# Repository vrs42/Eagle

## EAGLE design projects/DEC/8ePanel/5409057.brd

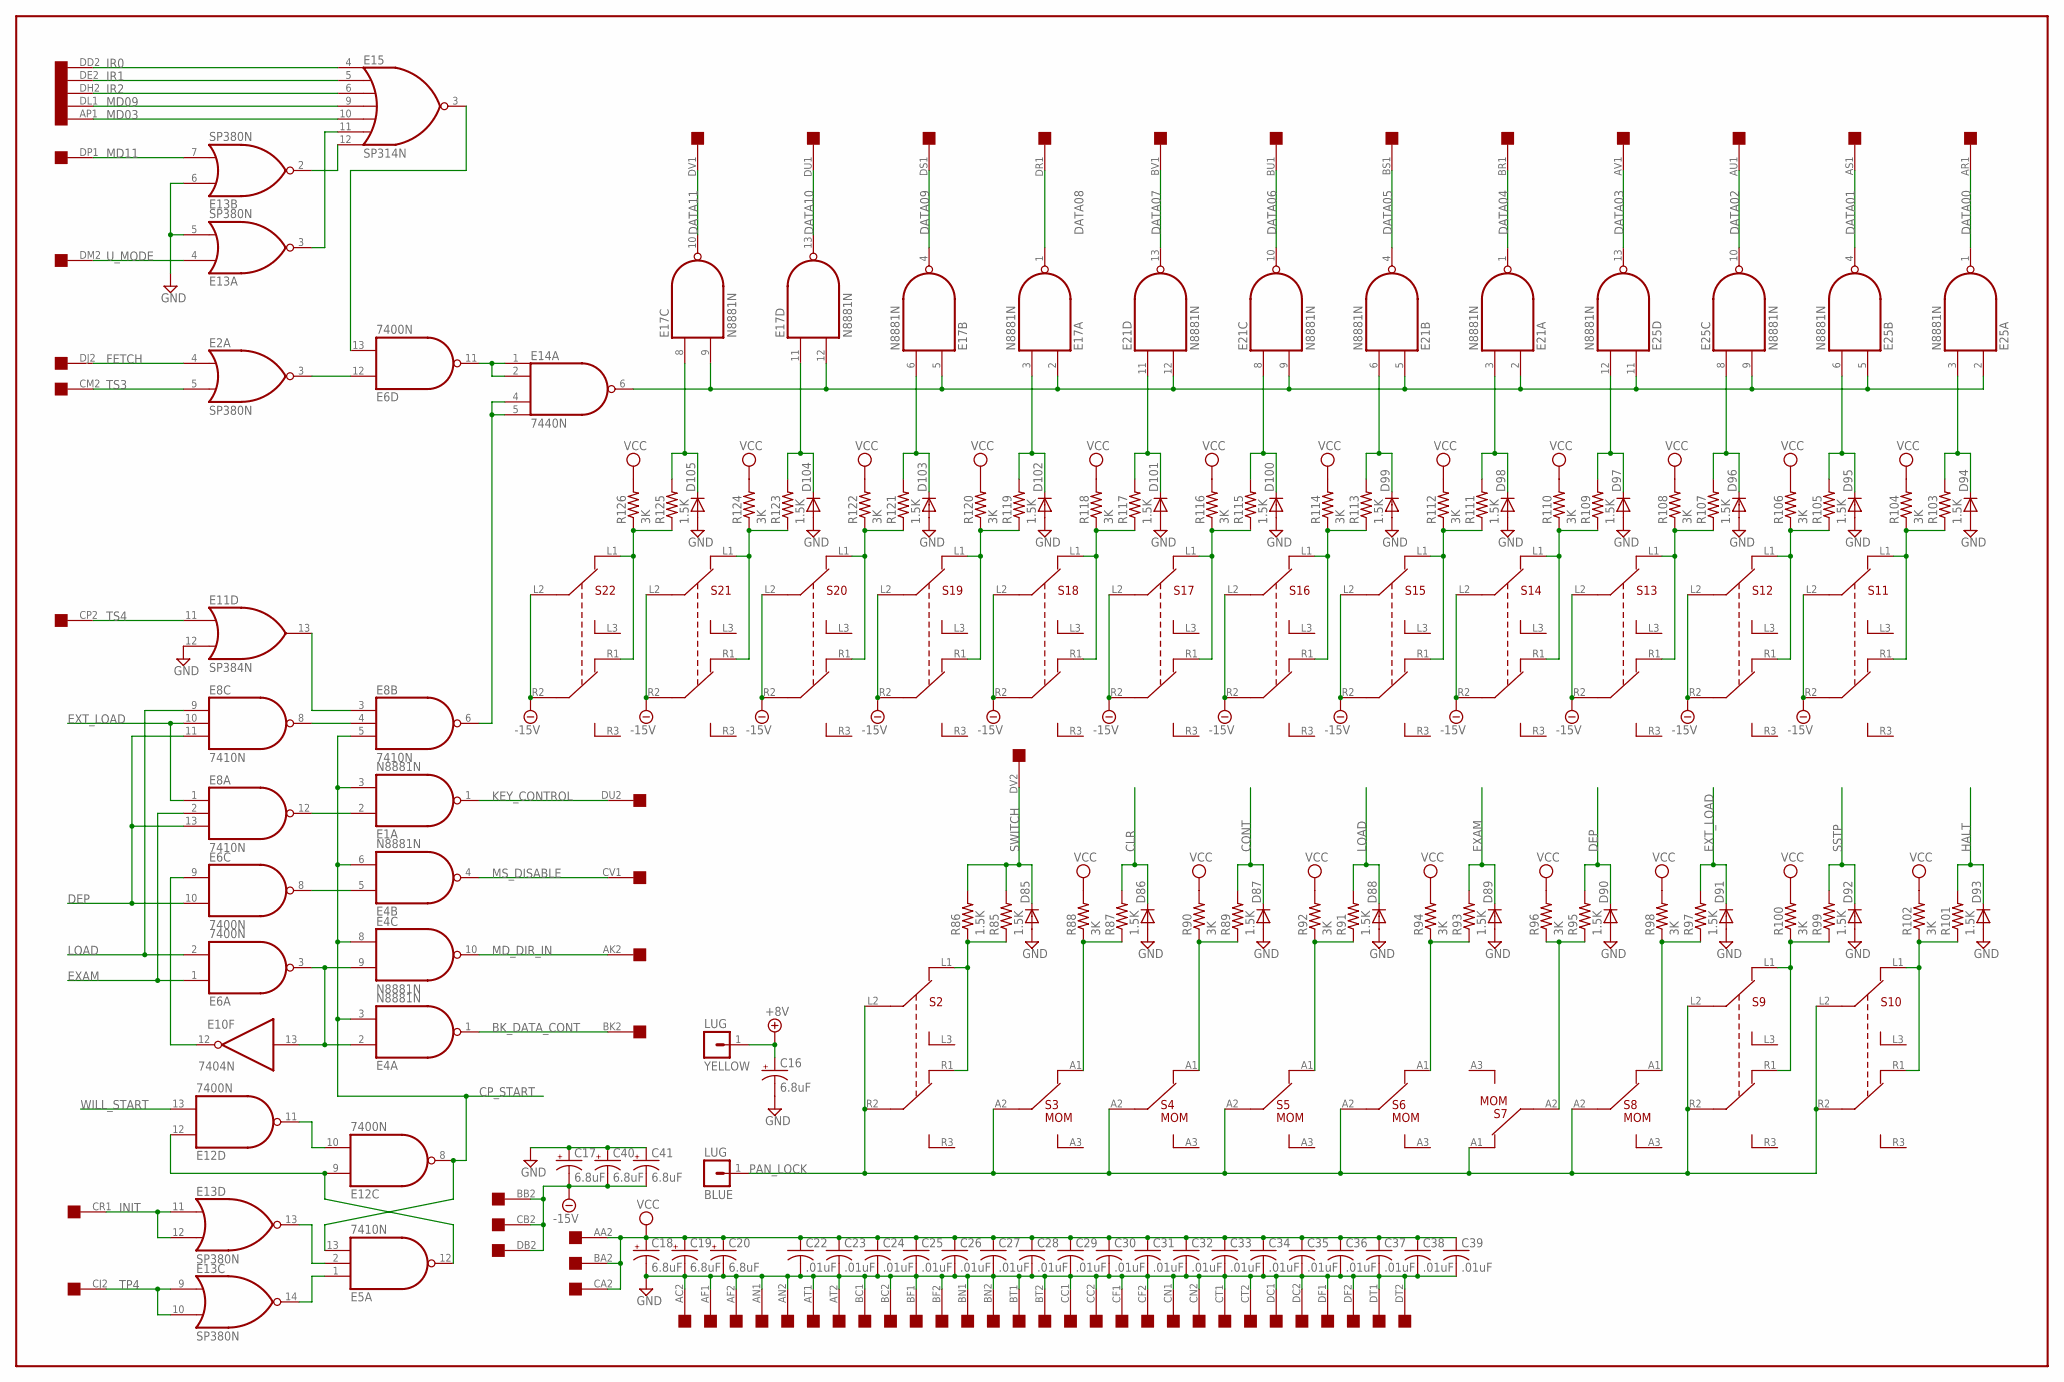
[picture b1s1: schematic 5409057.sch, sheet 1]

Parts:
BLUE: LUG; SPADELUG
C16, C17, C18, C19, C20, C40, C41: 6.8uF; E12-8
C22, C23, C24, C25, C26, C27, C28, C29, C30, C31, C32, C33, C34, C35, C36, C37, C38, C39: .01uF; C050-025X075
D85, D86, D87, D88, D89, D90, D91, D92, D93, D94, D95, D96, D97, D98, D99, D100, D101, D102, D103, D104, D105: 1N4148; DO35-10
E1, E4, E17, E21, E25: N8881N; DIL14
E2, E13: SP380N; DIL14
E5, E8: 7410N; DIL14
E6, E12: 7400N; DIL14
E10: 7404N; DIL14
E11: SP384N; DIL14
E14: 7440N; DIL14
E15: SP314N; DIL14
R85, R86, R87, R89, R91, R93, R95, R97, R99, R101, R103, R105, R107, R109, R111, R113, R115, R117, R119, R121, R123, R125: 1.5K; 0207/10
R88, R90, R92, R94, R96, R98, R100, R102, R104, R106, R108, R110, R112, R114, R116, R118, R120, R122, R124, R126: 3K; 0207/10
S2, S9, S10, S11, S12, S13, S14, S15, S16, S17, S18, S19, S20, S21, S22: DPDT8I
S3, S4, S5, S6, S7, S8: SPDT8I
U$2: QUAD; EDGE-CON8
YELLOW: LUG; SPADELUG

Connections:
+8V: C16.+, YELLOW.1; also elsewhere on the board
-15V: C17.-, C40.-, C41.-, S11.L2 (A2), S11.R2 (B2), S12.L2 (A2), S12.R2 (B2), S13.L2 (A2), S13.R2 (B2), S14.L2 (A2), S14.R2 (B2), S15.L2 (A2), S15.R2 (B2), S16.L2 (A2), S16.R2 (B2), S17.L2 (A2), S17.R2 (B2), S18.L2 (A2), S18.R2 (B2), S19.L2 (A2), S19.R2 (B2), S20.L2 (A2), S20.R2 (B2), S21.L2 (A2), S21.R2 (B2), S22.L2 (A2), S22.R2 (B2), U$2.BB2, U$2.CB2, U$2.DB2; also elsewhere on the board
BK_DATA_CONT: E4.1 (O), U$2.BK2; also elsewhere on the board
CLR: D86.C, R87.2; also elsewhere on the board
CONT: D87.C, R89.2; also elsewhere on the board
CP_START: E1.3 (I1), E4.3 (I1), E4.6 (I1), E4.8 (I0), E5.13 (I2), E8.5 (I2), E12.8 (O); also elsewhere on the board
DATA00: E25.1 (O), U$2.AR1; also elsewhere on the board
DATA01: E25.4 (O), U$2.AS1; also elsewhere on the board
DATA02: E25.10 (O), U$2.AU1; also elsewhere on the board
DATA03: E25.13 (O), U$2.AV1; also elsewhere on the board
DATA04: E21.1 (O), U$2.BR1; also elsewhere on the board
DATA05: E21.4 (O), U$2.BS1; also elsewhere on the board
DATA06: E21.10 (O), U$2.BU1; also elsewhere on the board
DATA07: E21.13 (O), U$2.BV1; also elsewhere on the board
DATA08: E17.1 (O), U$2.DR1; also elsewhere on the board
DATA09: E17.4 (O), U$2.DS1; also elsewhere on the board
DATA10: E17.13 (O), U$2.DU1; also elsewhere on the board
DATA11: E17.10 (O), U$2.DV1; also elsewhere on the board
DEP: D90.C, E6.10 (I1), E8.11 (I2), E8.13 (I2), R95.2; also elsewhere on the board
EXAM: D89.C, E6.1 (I0), E8.2 (I1), R93.2; also elsewhere on the board
EXT_LOAD: D91.C, E8.1 (I0), E8.10 (I1), R97.2; also elsewhere on the board
FETCH: E2.4 (I0), U$2.DJ2; also elsewhere on the board
GND: C16.-, C17.+, C18.-, C19.-, C20.-, C22.2, C23.2, C24.2, C25.2, C26.2, C27.2, C28.2, C29.2, C30.2, C31.2, C32.2, C33.2, C34.2, C35.2, C36.2, C37.2, C38.2, C39.2, C40.+, C41.+, D85.A, D86.A, D87.A, D88.A, D89.A, D90.A, D91.A, D92.A, D93.A, D94.A, D95.A, D96.A, D97.A, D98.A, D99.A, D100.A, D101.A, D102.A, D103.A, D104.A, D105.A, E1.7 (GND), E2.1 (GND), E4.7 (GND), E5.7 (GND), E6.7 (GND), E8.7 (GND), E10.7 (GND), E11.1 (GND), E11.12 (I1), E12.7 (GND), E13.1 (GND), E13.5 (I1), E13.6 (I0), E14.7 (GND), E15.1 (GND), E17.7 (GND), E21.7 (GND), E25.7 (GND), U$2.AC2, U$2.AF1, U$2.AF2, U$2.AN1, U$2.AN2, U$2.AT1, U$2.AT2, U$2.BC1, U$2.BC2, U$2.BF1, U$2.BF2, U$2.BN1, U$2.BN2, U$2.BT1, U$2.BT2, U$2.CC1, U$2.CC2, U$2.CF1, U$2.CF2, U$2.CN1, U$2.CN2, U$2.CT1, U$2.CT2, U$2.DC1, U$2.DC2, U$2.DF1, U$2.DF2, U$2.DT1, U$2.DT2; also elsewhere on the board
HALT: D93.C, R101.2; also elsewhere on the board
INIT: E13.11 (I0), E13.12 (I1), U$2.CR1; also elsewhere on the board
IR0: E15.4 (I0), U$2.DD2; also elsewhere on the board
IR1: E15.5 (I1), U$2.DE2; also elsewhere on the board
IR2: E15.6 (I2), U$2.DH2; also elsewhere on the board
KEY_CONTROL: E1.1 (O), U$2.DU2
LOAD: D88.C, E6.2 (I1), E8.9 (I0), R91.2; also elsewhere on the board
MD03: E15.10 (I4), U$2.AP1; also elsewhere on the board
MD09: E15.9 (I3), U$2.DL1; also elsewhere on the board
MD11: E13.7 (I1), U$2.DP1; also elsewhere on the board
MD_DIR_IN: E4.10 (O), U$2.AK2; also elsewhere on the board
MS_DISABLE: E4.4 (O), U$2.CV1
unnamed: E13.3 (O), E15.11 (I5)
unnamed: E13.2 (O), E15.12 (I6)
unnamed: E6.13 (I1), E15.3 (O)
unnamed: E2.3 (O), E6.12 (I0)
unnamed: E6.11 (O), E14.1 (I0), E14.2 (I1)
unnamed: E8.3 (I0), E11.13 (O)
unnamed: E14.6 (O), E17.2 (I0), E17.5 (I0), E17.9 (I1), E17.12 (I1), E21.2 (I0), E21.5 (I0), E21.9 (I1), E21.12 (I1), E25.2 (I0), E25.5 (I0), E25.9 (I1), E25.11 (I0)
unnamed: R125.1, R126.1, S22.L1 (A1), S22.R1 (B1)
unnamed: R121.1, R122.1, S20.L1 (A1), S20.R1 (B1)
unnamed: D105.C, E17.8 (I0), R125.2
unnamed: R123.1, R124.1, S21.L1 (A1), S21.R1 (B1)
unnamed: D103.C, E17.6 (I1), R121.2
unnamed: R117.1, R118.1, S18.L1 (A1), S18.R1 (B1)
unnamed: D104.C, E17.11 (I0), R123.2
unnamed: R119.1, R120.1, S19.L1 (A1), S19.R1 (B1)
unnamed: D101.C, E21.11 (I0), R117.2
unnamed: R109.1, R110.1, S14.L1 (A1), S14.R1 (B1)
unnamed: D102.C, E17.3 (I1), R119.2
unnamed: R115.1, R116.1, S17.L1 (A1), S17.R1 (B1)
unnamed: D97.C, E25.12 (I1), R109.2
unnamed: R85.1, R86.1, S2.L1 (A1), S2.R1 (B1)
unnamed: D100.C, E21.8 (I0), R115.2
unnamed: R87.1, R88.1, S3.A1
unnamed: R113.1, R114.1, S16.L1 (A1), S16.R1 (B1)
unnamed: D99.C, E21.6 (I1), R113.2
unnamed: R89.1, R90.1, S4.A1
unnamed: R111.1, R112.1, S15.L1 (A1), S15.R1 (B1)
unnamed: D98.C, E21.3 (I1), R111.2
unnamed: R91.1, R92.1, S5.A1
unnamed: R107.1, R108.1, S13.L1 (A1), S13.R1 (B1)
unnamed: D96.C, E25.8 (I0), R107.2
unnamed: R105.1, R106.1, S12.L1 (A1), S12.R1 (B1)
unnamed: D95.C, E25.6 (I1), R105.2
unnamed: R103.1, R104.1, S11.L1 (A1), S11.R1 (B1)
unnamed: D94.C, E25.3 (I1), R103.2
unnamed: E8.4 (I1), E8.8 (O)
unnamed: R93.1, R94.1, S6.A1
unnamed: E1.2 (I0), E8.12 (O)
unnamed: R95.1, R96.1, S7.A2
unnamed: E4.5 (I0), E6.8 (O)
unnamed: R99.1, R100.1, S9.L1 (A1), S9.R1 (B1)
unnamed: E4.2 (I0), E4.9 (I1), E6.3 (O), E10.13 (I)
unnamed: R101.1, R102.1, S10.L1 (A1), S10.R1 (B1)
unnamed: E6.9 (I0), E10.12 (O)
unnamed: R97.1, R98.1, S8.A1
unnamed: E8.6 (O), E14.4 (I2), E14.5 (I3)
unnamed: E5.2 (I1), E13.13 (O)
unnamed: E5.1 (I0), E13.14 (O)
unnamed: E5.12 (O), E12.9 (I0), E12.12 (I0)
unnamed: E12.10 (I1), E12.11 (O)
PAN_LOCK: BLUE.1, S2.L2 (A2), S2.R2 (B2), S3.A2, S4.A2, S5.A2, S6.A2, S7.A1, S8.A2, S9.L2 (A2), S9.R2 (B2), S10.L2 (A2), S10.R2 (B2)
SSTP: D92.C, R99.2; also elsewhere on the board
SWITCH: D85.C, R85.2, R86.2, U$2.DV2; also elsewhere on the board
TP4: E13.9 (I0), E13.10 (I1), U$2.CJ2
TS3: E2.5 (I1), U$2.CM2
TS4: E11.11 (I0), U$2.CP2
U_MODE: E13.4 (I0), U$2.DM2
VCC: C18.+, C19.+, C20.+, C22.1, C23.1, C24.1, C25.1, C26.1, C27.1, C28.1, C29.1, C30.1, C31.1, C32.1, C33.1, C34.1, C35.1, C36.1, C37.1, C38.1, C39.1, E1.14 (VCC), E2.8 (VCC), E4.14 (VCC), E5.14 (VCC), E6.14 (VCC), E8.14 (VCC), E10.14 (VCC), E11.8 (VCC), E12.14 (VCC), E13.8 (VCC), E14.14 (VCC), E15.8 (VCC), E17.14 (VCC), E21.14 (VCC), E25.14 (VCC), R88.2, R90.2, R92.2, R94.2, R96.2, R98.2, R100.2, R102.2, R104.2, R106.2, R108.2, R110.2, R112.2, R114.2, R116.2, R118.2, R120.2, R122.2, R124.2, R126.2, U$2.AA2, U$2.BA2, U$2.CA2; also elsewhere on the board
WILL_START: E12.13 (I1); also elsewhere on the board

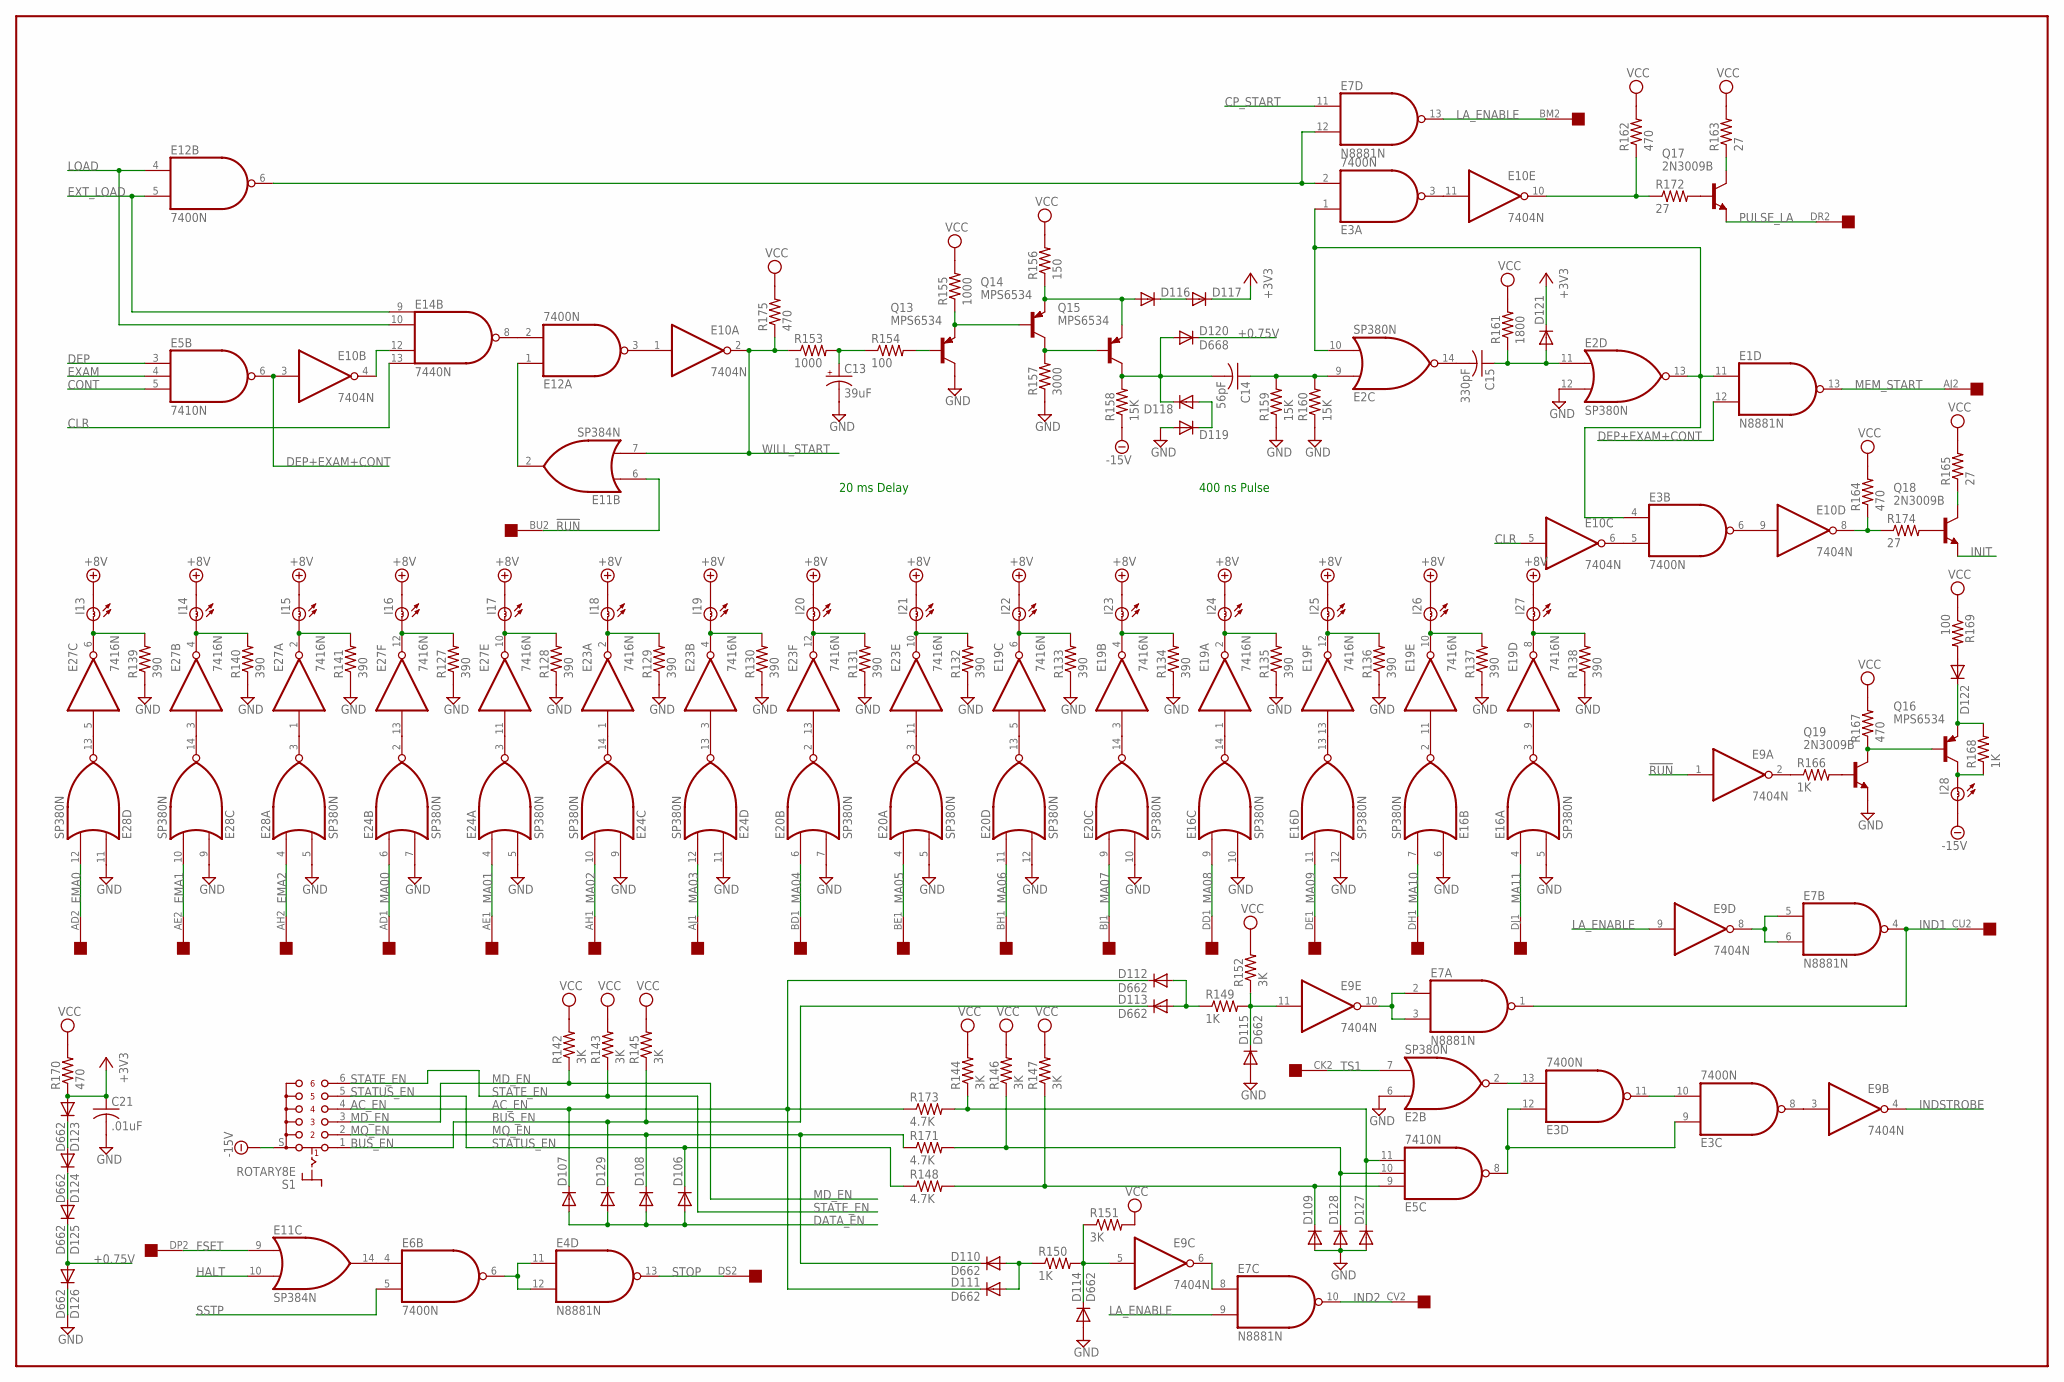
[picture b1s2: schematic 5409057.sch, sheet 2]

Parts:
C13: 39uF; E12-8
C14: 56pF; C050-025X075
C15: 330pF; C050-025X075
C21: .01uF; C050-025X075
D106, D107, D108, D109, D116, D117, D118, D119, D121, D122, D127, D128, D129: 1N4148; DO35-10
D110, D111, D112, D113, D114, D115, D123, D124, D125, D126: D662; DO35-10
D120: D668; DO35-10
E1, E4, E7: N8881N; DIL14
E2, E16, E20, E24, E28: SP380N; DIL14
E3, E6, E12: 7400N; DIL14
E5: 7410N; DIL14
E9, E10: 7404N; DIL14
E11: SP384N; DIL14
E14: 7440N; DIL14
E19, E23, E27: 7416N; DIL14
I13, I14, I15, I16, I17, I18, I19, I20, I21, I22, I23, I24, I25, I26, I27, I28: BULB
Q13, Q14, Q15, Q16: MPS6534; TO39
Q17, Q18, Q19: 2N3009B; TO39
R127, R128, R129, R130, R131, R132, R133, R134, R135, R136, R137, R138, R139, R140, R141: 390; 0207/10
R142, R143, R144, R145, R146, R147, R151, R152: 3K; 0207/10
R148, R171, R173: 4.7K; 0207/10
R149, R150, R166, R168: 1K; 0207/10
R153, R155: 1000; 0207/10
R154, R169: 100; 0207/10
R156: 150; 0207/10
R157: 3000; 0207/10
R158, R159, R160: 15K; 0207/10
R161: 1800; 0207/10
R162, R164, R167, R170: 470; 0207/10
R163, R165, R172, R174: 27; 0207/10
R175: 470; 0204/7
S1: ROTARY8E; ROTARY-8E
U$2: QUAD; EDGE-CON8

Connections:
!RUN: E9.1 (I), E11.6 (I0), U$2.BU2
+0.75V: D120.C, D125.C, D126.A
+3V3: C21.1, D117.C, D121.C, D123.A, R170.1
+8V: I13.B, I14.B, I15.B, I16.B, I17.B, I18.B, I19.B, I20.B, I21.B, I22.B, I23.B, I24.B, I25.B, I26.B, I27.B; also elsewhere on the board
-15V: I28.A, R158.1, S1.S; also elsewhere on the board
AC_EN: D107.C, D111.C, D112.C, R173.1, S1.4
BUS_EN: D113.C, D129.C, R145.1, S1.1
CLR: E10.5 (I), E14.13 (I3); also elsewhere on the board
CONT: E5.5 (I2); also elsewhere on the board
CP_START: E7.11 (I0); also elsewhere on the board
DATA_EN: D106.A, D107.A, D108.A, D129.A; also elsewhere on the board
DEP: E5.3 (I0); also elsewhere on the board
DEP+EXAM+CONT: E1.12 (I1), E5.6 (O), E10.3 (I)
EMA0: E28.12 (I1), U$2.AD2
EMA1: E28.10 (I1), U$2.AE2
EMA2: E28.4 (I0), U$2.AH2
EXAM: E5.4 (I1); also elsewhere on the board
EXT_LOAD: E12.5 (I1), E14.9 (I0); also elsewhere on the board
FSET: E11.9 (I0), U$2.DP2
GND: C13.-, C21.2, D109.A, D114.A, D115.A, D119.A, D126.C, D127.A, D128.A, E1.7 (GND), E2.1 (GND), E2.6 (I0), E2.12 (I1), E3.7 (GND), E4.7 (GND), E5.7 (GND), E6.7 (GND), E7.7 (GND), E9.7 (GND), E10.7 (GND), E11.1 (GND), E12.7 (GND), E14.7 (GND), E16.1 (GND), E16.5 (I1), E16.6 (I0), E16.10 (I1), E16.12 (I1), E19.7 (GND), E20.1 (GND), E20.5 (I1), E20.7 (I1), E20.10 (I1), E20.12 (I1), E23.7 (GND), E24.1 (GND), E24.5 (I1), E24.7 (I1), E24.9 (I0), E24.11 (I0), E27.7 (GND), E28.1 (GND), E28.5 (I1), E28.9 (I0), E28.11 (I0), Q13.3 (C), Q19.1 (E), R127.1, R128.1, R129.1, R130.1, R131.1, R132.1, R133.1, R134.1, R135.1, R136.1, R137.1, R138.1, R139.1, R140.1, R141.1, R157.1, R159.1, R160.1; also elsewhere on the board
HALT: E11.10 (I1); also elsewhere on the board
IND1: E7.1 (O), E7.4 (O), U$2.CU2
IND2: E7.10 (O), U$2.CV2
INDSTROBE: E9.4 (O); also elsewhere on the board
INIT: Q18.1 (E); also elsewhere on the board
LA_ENABLE: E7.9 (I1), E7.13 (O), E9.9 (I), U$2.BM2
LOAD: E12.4 (I0), E14.10 (I1); also elsewhere on the board
MA00: E24.6 (I0), U$2.AD1
MA01: E24.4 (I0), U$2.AE1
MA02: E24.10 (I1), U$2.AH1
MA03: E24.12 (I1), U$2.AJ1
MA04: E20.6 (I0), U$2.BD1
MA05: E20.4 (I0), U$2.BE1
MA06: E20.11 (I0), U$2.BH1
MA07: E20.9 (I0), U$2.BJ1
MA08: E16.9 (I0), U$2.DD1
MA09: E16.11 (I0), U$2.DE1
MA10: E16.7 (I1), U$2.DH1
MA11: E16.4 (I0), U$2.DJ1
MD_EN: R142.1, S1.3; also elsewhere on the board
MEM_START: E1.13 (O), U$2.AJ2
MQ_EN: D108.C, D110.C, R171.1, S1.2
unnamed: E27.10 (O), I17.A, R128.2
unnamed: E10.4 (O), E14.12 (I2)
unnamed: E12.2 (I1), E14.8 (O)
unnamed: E10.1 (I), E12.3 (O)
unnamed: E11.2 (O), E12.1 (I0)
unnamed: C13.+, R153.2, R154.1
unnamed: Q13.2 (B), R154.2
unnamed: Q13.1 (E), Q14.2 (B), R155.1
unnamed: D116.A, Q14.1 (E), Q15.1 (E), R156.1
unnamed: Q14.3 (C), Q15.2 (B), R157.2
unnamed: C14.2, D118.C, D120.A, Q15.3 (C), R158.2
unnamed: D116.C, D117.A
unnamed: C14.1, E2.9 (I0), R159.2, R160.2
unnamed: D118.A, D119.C
unnamed: C15.2, E2.14 (O)
unnamed: C15.1, D121.A, E2.11 (I0), R161.1
unnamed: E1.11 (I0), E2.10 (I1), E2.13 (O), E3.1 (I0), E3.4 (I0)
unnamed: E3.2 (I1), E7.12 (I1), E12.6 (O)
unnamed: E3.3 (O), E10.11 (I)
unnamed: Q17.2 (B), R172.2
unnamed: Q17.3 (C), R163.1
unnamed: E10.10 (O), R162.1, R172.1
unnamed: D127.C, E5.11 (I2), R144.1, R173.2
unnamed: E27.6 (O), I13.A, R139.2
unnamed: E27.5 (I), E28.13 (O)
unnamed: E27.4 (O), I14.A, R140.2
unnamed: E27.2 (O), I15.A, R141.2
unnamed: E27.12 (O), I16.A, R127.2
unnamed: E27.3 (I), E28.14 (O)
unnamed: E27.1 (I), E28.3 (O)
unnamed: E24.2 (O), E27.13 (I)
unnamed: E6.4 (I0), E11.14 (O)
unnamed: E23.2 (O), I18.A, R129.2
unnamed: E23.4 (O), I19.A, R130.2
unnamed: E23.12 (O), I20.A, R131.2
unnamed: E23.10 (O), I21.A, R132.2
unnamed: E19.6 (O), I22.A, R133.2
unnamed: E19.4 (O), I23.A, R134.2
unnamed: E19.2 (O), I24.A, R135.2
unnamed: E24.3 (O), E27.11 (I)
unnamed: E23.1 (I), E24.14 (O)
unnamed: E23.3 (I), E24.13 (O)
unnamed: E19.12 (O), I25.A, R136.2
unnamed: E19.10 (O), I26.A, R137.2
unnamed: E19.8 (O), I27.A, R138.2
unnamed: Q18.3 (C), R165.1
unnamed: E20.2 (O), E23.13 (I)
unnamed: E20.3 (O), E23.11 (I)
unnamed: E19.5 (I), E20.13 (O)
unnamed: E19.3 (I), E20.14 (O)
unnamed: E16.14 (O), E19.1 (I)
unnamed: E16.13 (O), E19.13 (I)
unnamed: E16.2 (O), E19.11 (I)
unnamed: E16.3 (O), E19.9 (I)
unnamed: E2.2 (O), E3.13 (I1)
unnamed: E3.9 (I0), E3.12 (I0), E5.8 (O)
unnamed: E3.10 (I1), E3.11 (O)
unnamed: E3.8 (O), E9.3 (I)
unnamed: E3.6 (O), E10.9 (I)
unnamed: E4.11 (I0), E4.12 (I1), E6.6 (O)
unnamed: E7.5 (I0), E7.6 (I1), E9.8 (O)
unnamed: E7.2 (I0), E7.3 (I1), E9.10 (O)
unnamed: E7.8 (I0), E9.6 (O)
unnamed: E3.5 (I1), E10.6 (O)
unnamed: E9.2 (O), R166.1
unnamed: D124.C, D125.A
unnamed: D123.C, D124.A
unnamed: Q19.2 (B), R166.2
unnamed: Q16.2 (B), Q19.3 (C), R167.1
unnamed: D122.A, R169.2
unnamed: D122.C, Q16.1 (E), R168.2
unnamed: I28.B, Q16.3 (C), R168.1
unnamed: E10.8 (O), R164.1, R174.1
unnamed: Q18.2 (B), R174.2
unnamed: D110.A, D111.A, R150.1
unnamed: D114.C, E9.5 (I), R150.2, R151.1
unnamed: D112.A, D113.A, R149.1
unnamed: D115.C, E9.11 (I), R149.2, R152.1
unnamed: D128.C, E5.10 (I1), R146.1, R171.2
unnamed: D109.C, E5.9 (I0), R147.1, R148.2
PULSE_LA: Q17.1 (E), U$2.DR2
SSTP: E6.5 (I1); also elsewhere on the board
STATE_EN: R143.1, S1.6; also elsewhere on the board
STATUS_EN: D106.C, R148.1, S1.5
STOP: E4.13 (O), U$2.DS2
TS1: E2.7 (I1), U$2.CK2
VCC: E1.14 (VCC), E2.8 (VCC), E3.14 (VCC), E4.14 (VCC), E5.14 (VCC), E6.14 (VCC), E7.14 (VCC), E9.14 (VCC), E10.14 (VCC), E11.8 (VCC), E12.14 (VCC), E14.14 (VCC), E16.8 (VCC), E19.14 (VCC), E20.8 (VCC), E23.14 (VCC), E24.8 (VCC), E27.14 (VCC), E28.8 (VCC), R142.2, R143.2, R144.2, R145.2, R146.2, R147.2, R151.2, R152.2, R155.2, R156.2, R161.2, R162.2, R163.2, R164.2, R165.2, R167.2, R169.1, R170.2, R175.2; also elsewhere on the board
WILL_START: E10.2 (O), E11.7 (I1), R153.1, R175.1; also elsewhere on the board

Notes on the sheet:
20 ms Delay
400 ns Pulse

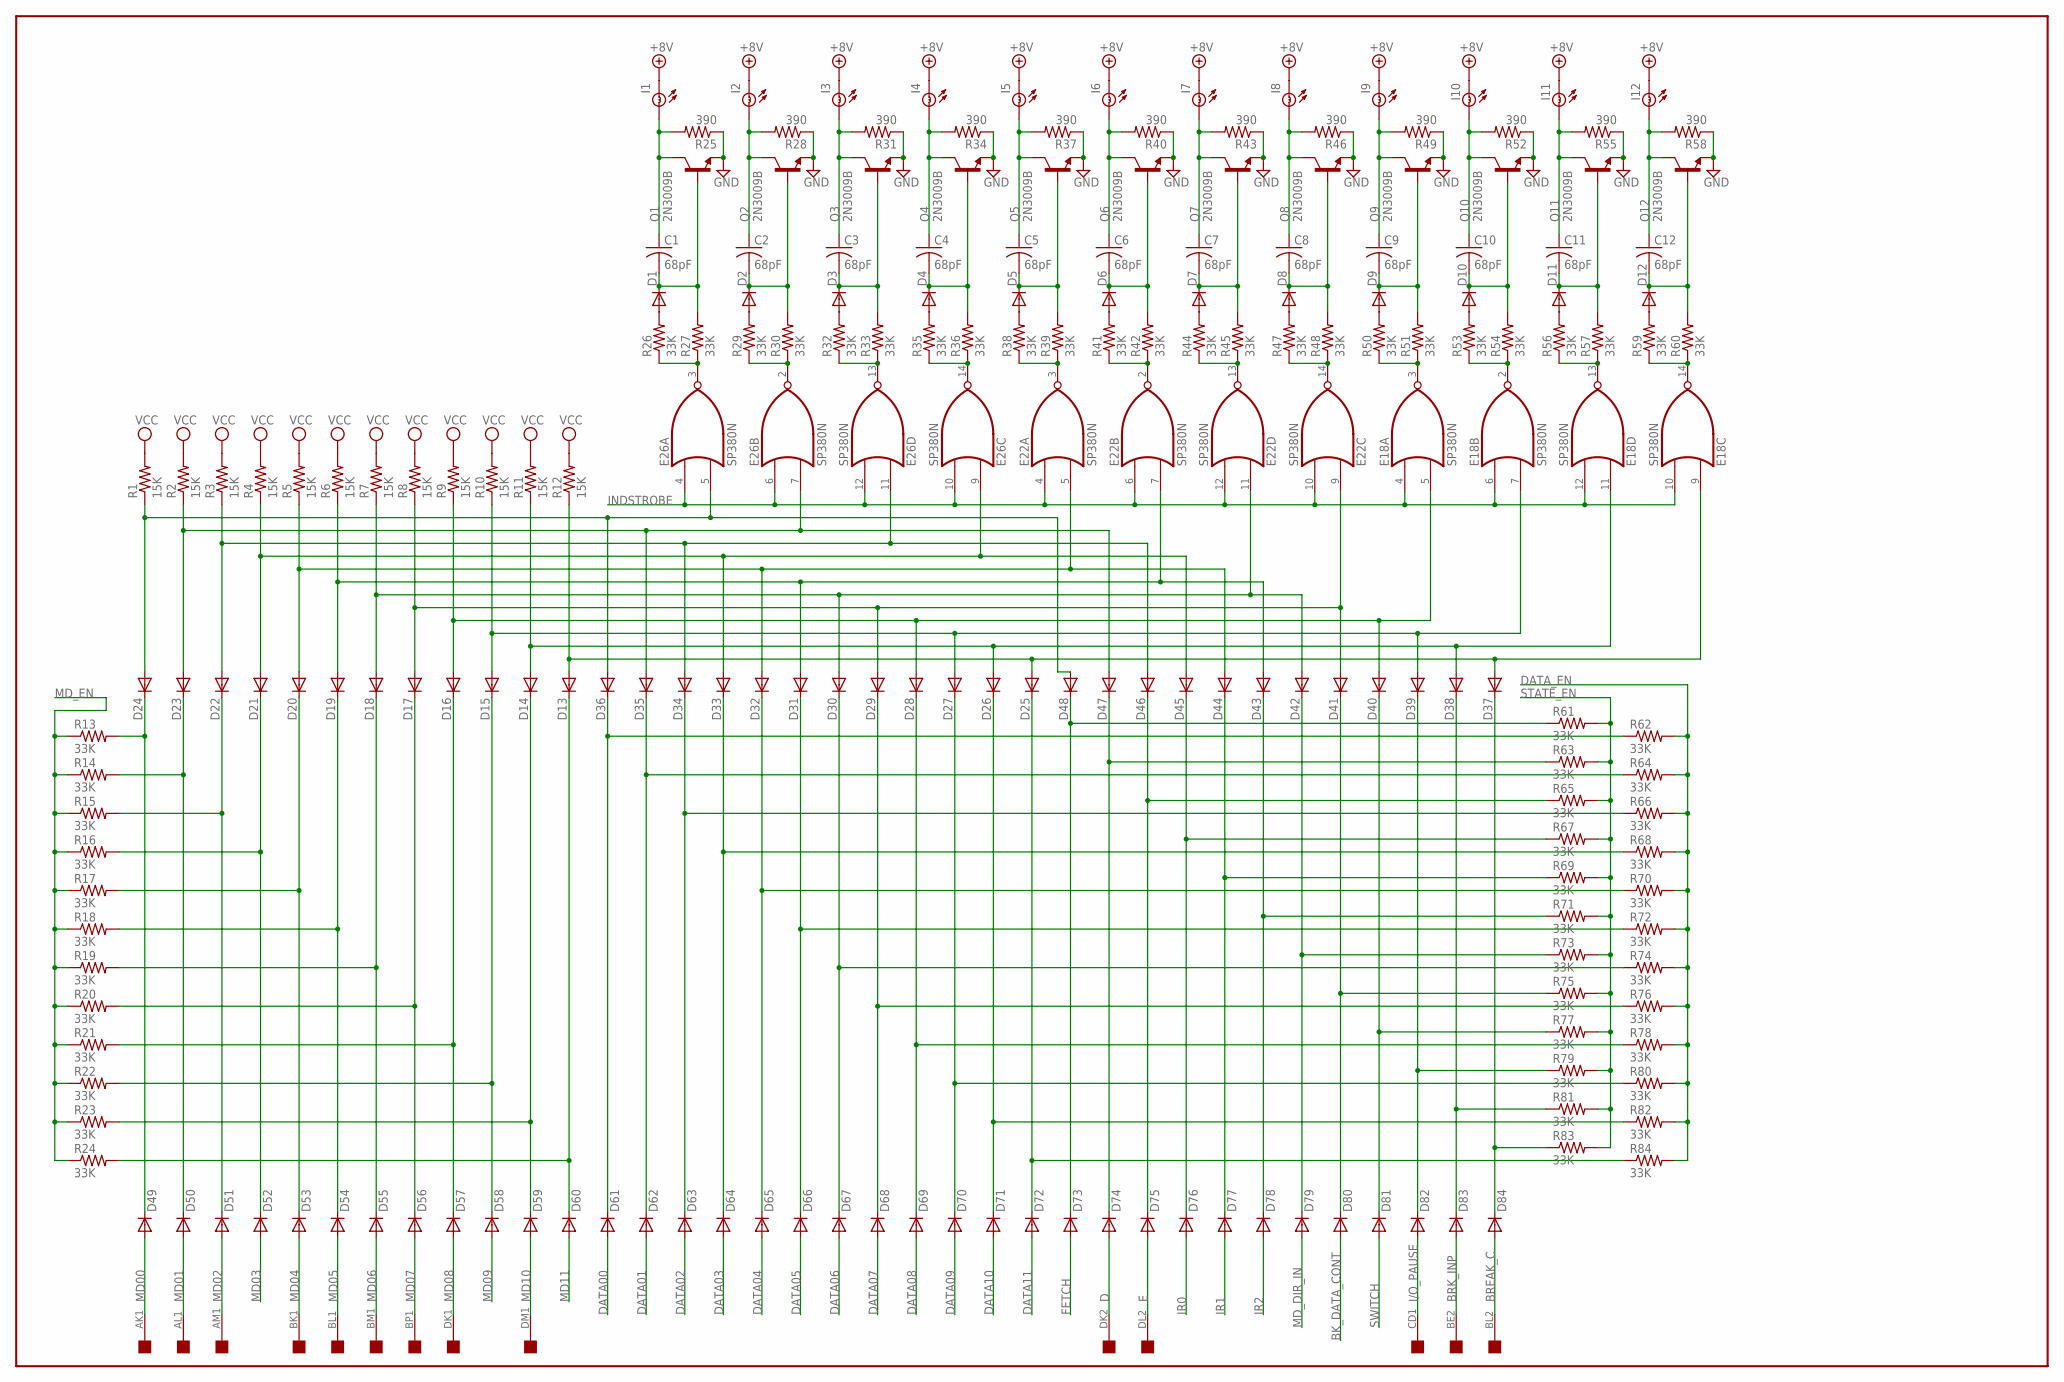
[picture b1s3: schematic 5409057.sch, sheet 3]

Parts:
C1, C2, C3, C4, C5, C6, C7, C8, C9, C10, C11, C12: 68pF; C050-025X075
D1, D2, D3, D4, D5, D6, D7, D8, D9, D10, D11, D12, D13, D14, D15, D16, D17, D18, D19, D20, D21, D22, D23, D24, D25, D26, D27, D28, D29, D30, D31, D32, D33, D34, D35, D36, D37, D38, D39, D40, D41, D42, D43, D44, D45, D46, D47, D48, D49, D50, D51, D52, D53, D54, D55, D56, D57, D58, D59, D60, D61, D62, D63, D64, D65, D66, D67, D68, D69, D70, D71, D72, D73, D74, D75, D76, D77, D78, D79, D80, D81, D82, D83, D84: 1N4148; DO35-10
E18, E22, E26: SP380N; DIL14
I1, I2, I3, I4, I5, I6, I7, I8, I9, I10, I11, I12: BULB
Q1, Q2, Q3, Q4, Q5, Q6, Q7, Q8, Q9, Q10, Q11, Q12: 2N3009B; TO39
R1, R2, R3, R4, R5, R6, R7, R8, R9, R10, R11, R12: 15K; 0207/10
R13, R14, R15, R16, R17, R18, R19, R20, R21, R22, R23, R24, R26, R27, R29, R30, R32, R33, R35, R36, R38, R39, R41, R42, R44, R45, R47, R48, R50, R51, R53, R54, R56, R57, R59, R60, R61, R62, R63, R64, R65, R66, R67, R68, R69, R70, R71, R72, R73, R74, R75, R76, R77, R78, R79, R80, R81, R82, R83, R84: 33K; 0207/10
R25, R28, R31, R34, R37, R40, R43, R46, R49, R52, R55, R58: 390; 0207/10
U$2: QUAD; EDGE-CON8

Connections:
+8V: I1.B, I2.B, I3.B, I4.B, I5.B, I6.B, I7.B, I8.B, I9.B, I10.B, I11.B, I12.B; also elsewhere on the board
BK_DATA_CONT: D80.A; also elsewhere on the board
BREAK_C: D84.A, U$2.BL2
BRK_INP: D83.A, U$2.BE2
D: D74.A, U$2.DK2
DATA00: D61.A; also elsewhere on the board
DATA01: D62.A; also elsewhere on the board
DATA02: D63.A; also elsewhere on the board
DATA03: D64.A; also elsewhere on the board
DATA04: D65.A; also elsewhere on the board
DATA05: D66.A; also elsewhere on the board
DATA06: D67.A; also elsewhere on the board
DATA07: D68.A; also elsewhere on the board
DATA08: D69.A; also elsewhere on the board
DATA09: D70.A; also elsewhere on the board
DATA10: D71.A; also elsewhere on the board
DATA11: D72.A; also elsewhere on the board
DATA_EN: R62.2, R64.2, R66.2, R68.2, R70.2, R72.2, R74.2, R76.2, R78.2, R80.2, R82.2, R84.2; also elsewhere on the board
E: D75.A, U$2.DL2
FETCH: D73.A; also elsewhere on the board
GND: E18.1 (GND), E22.1 (GND), E26.1 (GND), Q1.1 (E), Q2.1 (E), Q3.1 (E), Q4.1 (E), Q5.1 (E), Q6.1 (E), Q7.1 (E), Q8.1 (E), Q9.1 (E), Q10.1 (E), Q11.1 (E), Q12.1 (E), R25.1, R28.1, R31.1, R34.1, R37.1, R40.1, R43.1, R46.1, R49.1, R52.1, R55.1, R58.1; also elsewhere on the board
I/O_PAUSE: D82.A, U$2.CD1
INDSTROBE: E18.4 (I0), E18.6 (I0), E18.10 (I1), E18.12 (I1), E22.4 (I0), E22.6 (I0), E22.10 (I1), E22.12 (I1), E26.4 (I0), E26.6 (I0), E26.10 (I1), E26.12 (I1); also elsewhere on the board
IR0: D76.A; also elsewhere on the board
IR1: D77.A; also elsewhere on the board
IR2: D78.A; also elsewhere on the board
MD00: D49.A, U$2.AK1
MD01: D50.A, U$2.AL1
MD02: D51.A, U$2.AM1
MD03: D52.A; also elsewhere on the board
MD04: D53.A, U$2.BK1
MD05: D54.A, U$2.BL1
MD06: D55.A, U$2.BM1
MD07: D56.A, U$2.BP1
MD08: D57.A, U$2.DK1
MD09: D58.A; also elsewhere on the board
MD10: D59.A, U$2.DM1
MD11: D60.A; also elsewhere on the board
MD_DIR_IN: D79.A; also elsewhere on the board
MD_EN: R13.1, R14.1, R15.1, R16.1, R17.1, R18.1, R19.1, R20.1, R21.1, R22.1, R23.1, R24.1; also elsewhere on the board
unnamed: E26.3 (O), R26.1, R27.1
unnamed: D1.A, R26.2
unnamed: C1.2, D1.C, Q1.2 (B), R27.2
unnamed: C1.1, I1.A, Q1.3 (C), R25.2
unnamed: E26.2 (O), R29.1, R30.1
unnamed: D2.A, R29.2
unnamed: C2.2, D2.C, Q2.2 (B), R30.2
unnamed: C2.1, I2.A, Q2.3 (C), R28.2
unnamed: E26.13 (O), R32.1, R33.1
unnamed: D3.A, R32.2
unnamed: C3.2, D3.C, Q3.2 (B), R33.2
unnamed: C3.1, I3.A, Q3.3 (C), R31.2
unnamed: E26.14 (O), R35.1, R36.1
unnamed: D4.A, R35.2
unnamed: C4.2, D4.C, Q4.2 (B), R36.2
unnamed: C4.1, I4.A, Q4.3 (C), R34.2
unnamed: E22.3 (O), R38.1, R39.1
unnamed: D5.A, R38.2
unnamed: C5.2, D5.C, Q5.2 (B), R39.2
unnamed: C5.1, I5.A, Q5.3 (C), R37.2
unnamed: E22.2 (O), R41.1, R42.1
unnamed: D6.A, R41.2
unnamed: C6.2, D6.C, Q6.2 (B), R42.2
unnamed: C6.1, I6.A, Q6.3 (C), R40.2
unnamed: E22.13 (O), R44.1, R45.1
unnamed: D7.A, R44.2
unnamed: C7.2, D7.C, Q7.2 (B), R45.2
unnamed: C7.1, I7.A, Q7.3 (C), R43.2
unnamed: E22.14 (O), R47.1, R48.1
unnamed: D8.A, R47.2
unnamed: C8.2, D8.C, Q8.2 (B), R48.2
unnamed: C8.1, I8.A, Q8.3 (C), R46.2
unnamed: E18.3 (O), R50.1, R51.1
unnamed: D9.A, R50.2
unnamed: C9.2, D9.C, Q9.2 (B), R51.2
unnamed: C9.1, I9.A, Q9.3 (C), R49.2
unnamed: E18.2 (O), R53.1, R54.1
unnamed: D10.A, R53.2
unnamed: C10.2, D10.C, Q10.2 (B), R54.2
unnamed: C10.1, I10.A, Q10.3 (C), R52.2
unnamed: E18.13 (O), R56.1, R57.1
unnamed: D11.A, R56.2
unnamed: C11.2, D11.C, Q11.2 (B), R57.2
unnamed: C11.1, I11.A, Q11.3 (C), R55.2
unnamed: E18.14 (O), R59.1, R60.1
unnamed: D12.A, R59.2
unnamed: C12.2, D12.C, Q12.2 (B), R60.2
unnamed: C12.1, I12.A, Q12.3 (C), R58.2
unnamed: D24.A, D36.A, D48.A, E26.5 (I1), R1.1
unnamed: D23.A, D35.A, D47.A, E26.7 (I1), R2.1
unnamed: D22.A, D34.A, D46.A, E26.11 (I0), R3.1
unnamed: D21.A, D33.A, D45.A, E26.9 (I0), R4.1
unnamed: D20.A, D32.A, D44.A, E22.5 (I1), R5.1
unnamed: D19.A, D31.A, D43.A, E22.7 (I1), R6.1
unnamed: D18.A, D30.A, D42.A, E22.11 (I0), R7.1
unnamed: D17.A, D29.A, D41.A, E22.9 (I0), R8.1
unnamed: D16.A, D28.A, D40.A, E18.5 (I1), R9.1
unnamed: D15.A, D27.A, D39.A, E18.7 (I1), R10.1
unnamed: D14.A, D26.A, D38.A, E18.11 (I0), R11.1
unnamed: D13.A, D25.A, D37.A, E18.9 (I0), R12.1
unnamed: D24.C, D49.C, R13.2
unnamed: D13.C, D60.C, R24.2
unnamed: D14.C, D59.C, R23.2
unnamed: D15.C, D58.C, R22.2
unnamed: D16.C, D57.C, R21.2
unnamed: D17.C, D56.C, R20.2
unnamed: D18.C, D55.C, R19.2
unnamed: D19.C, D54.C, R18.2
unnamed: D23.C, D50.C, R14.2
unnamed: D22.C, D51.C, R15.2
unnamed: D21.C, D52.C, R16.2
unnamed: D20.C, D53.C, R17.2
unnamed: D36.C, D61.C, R62.1
unnamed: D35.C, D62.C, R64.1
unnamed: D34.C, D63.C, R66.1
unnamed: D33.C, D64.C, R68.1
unnamed: D32.C, D65.C, R70.1
unnamed: D31.C, D66.C, R72.1
unnamed: D30.C, D67.C, R74.1
unnamed: D29.C, D68.C, R76.1
unnamed: D28.C, D69.C, R78.1
unnamed: D27.C, D70.C, R80.1
unnamed: D26.C, D71.C, R82.1
unnamed: D25.C, D72.C, R84.1
unnamed: D48.C, D73.C, R61.1
unnamed: D47.C, D74.C, R63.1
unnamed: D46.C, D75.C, R65.1
unnamed: D45.C, D76.C, R67.1
unnamed: D44.C, D77.C, R69.1
unnamed: D43.C, D78.C, R71.1
unnamed: D42.C, D79.C, R73.1
unnamed: D41.C, D80.C, R75.1
unnamed: D40.C, D81.C, R77.1
unnamed: D39.C, D82.C, R79.1
unnamed: D38.C, D83.C, R81.1
unnamed: D37.C, D84.C, R83.1
STATE_EN: R61.2, R63.2, R65.2, R67.2, R69.2, R71.2, R73.2, R75.2, R77.2, R79.2, R81.2, R83.2; also elsewhere on the board
SWITCH: D81.A; also elsewhere on the board
VCC: E18.8 (VCC), E22.8 (VCC), E26.8 (VCC), R1.2, R2.2, R3.2, R4.2, R5.2, R6.2, R7.2, R8.2, R9.2, R10.2, R11.2, R12.2; also elsewhere on the board
